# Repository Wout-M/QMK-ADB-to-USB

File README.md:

# QMK ADB to USB Converter
A custom ADB to USB Converter with an OLED screen, made with QMK, for my vintage [Apple Standard Keyboard](https://deskthority.net/wiki/Apple_Standard_Keyboard)

Special thanks to [tzarc](https://github.com/tzarc) for making the firmware of the converter & [ronangaillard](https://github.com/ronangaillard) for making the PCB.

## About the project
This all started when I wanted to try out vintage mechanical keyboards and found an Apple Standard Keyboard on a second hand site for cheap. Documentation & resources about converters that I found was very spread out or old so I decided to centralize my findings on here for if other people would try the same.

## Goals
- Being able to connect the keyboard with USB, preferably USB-C
- Fully programmable with multiple layers with QMK
- Display info about the current layer and capslock & numlock on an OLED screen

## Firmware
Using QMK was a must for me to have the keyboard be easily programmable (and already having a little experience with it helped too). Luckily, someone else also made [a converter](https://github.com/qmk/qmk_firmware/tree/master/keyboards/converter/adb_usb) on the QMK repository that I needed to customize for use with an OLED screen and the Apple Standard Keyboard (it was made mainly for the Apple Extended Keyboard).

### Wiring
For wiring the ADB socket to the Arduino, only 3 wires are necessary for conversion (the power SW pin is not used): 

      ,--_--.
     / o4 3o \      1: DATA
    | o2   1o |     2: Power SW
     -  ===  -      3: VCC
      `-___-'       4: GND

    Keyboard       Converter
                   ,------.
    VCC-----+------|5V    |
            |      |      |
           [R]     |      |
            |      |      |
    DATA----+------|PD0   |
                   |      |
    GND------------|GND   |
                   `------'
    R: 1K Ohm resistor

I'll be using an Arduino Pro Micro for this, where pin PD0 is pin 3 (D0 on the image).

Sadly, this pin is also for I2C communication (which I will need for the OLED screen), but luckily the pin for the converter can be customized by changing the value for `ADB_DATA_BIT` in `config.h` where 0 stands for pin PD0 so changing it to 2 will make it use pin PD2 (pin 0 on the Pro Micro).

For the OLED screen I'll be using pins 2 (SDA) and 3 (SCL) for the I2C communication. This also requires adding a few things in the firmware files:
- `rules.mk`: Add `OLED_ENABLE = yes`
- `config.h`: If any changes need to be made to QMK's default OLED configuration, they should be made here. I added `#define OLED_TIMEOUT 0` to have the screen always on
- `keymap.c`: In your keymap file you'll need to add the necessary functions to display what you want on the screen.
    ```c
    #ifdef OLED_ENABLE

    bool oled_task_user(void) {
        // Host Keyboard Layer Status
        // oled_write_P(PSTR("Layer: "), false);

        switch (get_highest_layer(layer_state)) {
            case 0:
                oled_write_ln_P(PSTR("DEFAULT\n"), false);
                break;
            case 1:
                oled_write_ln_P(PSTR("FUNCTION\n"), false);
                break;
            default:
                // Or use the write_ln shortcut over adding '\n' to the end of your string
                oled_write_ln_P(PSTR("Undefined"), false);
        }

        // Host Keyboard LED Status
        led_t led_state = host_keyboard_led_state();
        oled_write_P(led_state.num_lock ? PSTR("NUM ") : PSTR("    "), false);
        oled_write_P(led_state.caps_lock ? PSTR("CAP ") : PSTR("    "), false);
        oled_write_P(led_state.scroll_lock ? PSTR("SCR ") : PSTR("    "), false);
        
        return false;
    }

    oled_rotation_t oled_init_user(oled_rotation_t rotation) {
        return OLED_ROTATION_180;  // flips the display 180 degrees if offhand
    }

    #endif
    ```

### Layers
Since the Apple Standard Keyboard doesn't have a function row and the extra buttons of a full sized keyboard (home, end, pg up/down, ...) that I use while developing, I wanted to have atleast 2 layers.

One with the normal keys shown on the keycaps

And one with all the special keys

### Building the firmware
In the [QMK docs](https://docs.qmk.fm) you can find plenty of information on what you'll need to be able to build the firmware and how to flash it, but in short you'll need:

- `QMK MSYS`: For building the firmware. 
    - Use `qmk setup` for setting up the qmk_firmware folder where all keyboards, keymaps & logic is contained. By default it's installed under your user folder.
    - For the converter code, you'll find it at `keyboards/converter/adb_usb` (and replace the files with those from this repo if you want to use my code)
    - I've used the following command to build the firmware: `qmk compile -kb converter/adb_usb/rev1 -km default`
- `QMK Toolbox`: For flashing the firmware onto the Arduino
- Some IDE or text editor for customizing the firmware, I've used `Visual Studio Code`

## Converter
I couldn't just leave an Arduino, a port, a resistors and some wires dangling between my keyboard and my pc (even though that's what I did for a while), so I went looking into making a PCB design. 

### PCB
Luckily, once again, [somebody else](https://github.com/ronangaillard/adb2usb) made *almost* what I needed. A PCB for the Arduino Pro Micro and the ADB port, but without the OLED screen connection.

With some slight modifications to the wiring for using a different pin for the conversion and adding the connections for the OLED screen, it looks like this:

### Parts
| Part name                                                                                                 | Price  |
| ----------------------------------------------------------------------------------------------------------| :----: |
| [Arduino Pro Micro clone](https://www.aliexpress.com/item/1005005967686665.html)                          | €3,71  |
| [Mini-Din 4-pin connector](https://www.aliexpress.com/item/1005004227811305.) (same shape as an ADB port) | €3,60  |
| [OLED screen](https://www.aliexpress.com/item/1005005865476967.html)                                      | €2,11  |
| [Resistor](https://www.aliexpress.com/item/32505894332.html)                                              | €1,58  |
| Custom PCB (ordered from [JLCPCB](https://jlcpcb.com/))                                                   | €1,83  |

*The list is excluding shipping cost and prices may change over time. Some parts (like the resistors) were purchased more than what I need so I would have some spares/stock.*

## Housing
I wanted the converter to be easily clipped on to the keyboard so it wouldn't get anywhere while using it while also not modifying the keyboard itself. The housing consists of 3 parts: the clip, the converter housing that slots into the clip and the OLED housing that slots into the converter housing. Everything was made with [OnShape](https://www.onshape.com).

## Build Log
### 5 September 2023
The keyboard was acquired and the idea was born.

Some inspection to see if the board itself still looks good:

### 11 November 2023
After a small hiatus & many evenings of research and trying out different things, the keyboard finally works.

For now, the converter is held together with wires and tape, but the initial PCB (without OLED) is on it's way.

Now the deep cleaning of the keyboard can start (30 years worth of dust and grime isn't going to come off by itself). I can highly recommend [this video](https://www.youtube.com/watch?v=RnvC80Vjuts) for tips on how to clean vintage keyboards. 

I've used lots of Q-tips & isopropyl alcohol for the keyboard itself and a soap bath of a couple days for the keycaps. One of the keycaps on the numpad was sadly severely damaged on the inside (the pin was glued on with hot glue) so I decided to leave it off since I won't use it anyways.

### 4 December 2023
After a long wait, and some problems with delivery, the PCB with the OLED connector is here.

I recommend using some male & female pin headers for the OLED screen. This way you can just slide the screen in the top housing and easily put it on or take it off without worrying about breaking connections.

### 8 December 2023
Thanks to my Ender 3 and some evenings on OnShape, the full housing is now finished to and I can actually properly use my keyboard instead of having a taped together wire & bare electronics mess.

I've been using this keyboard every day at work ever since.

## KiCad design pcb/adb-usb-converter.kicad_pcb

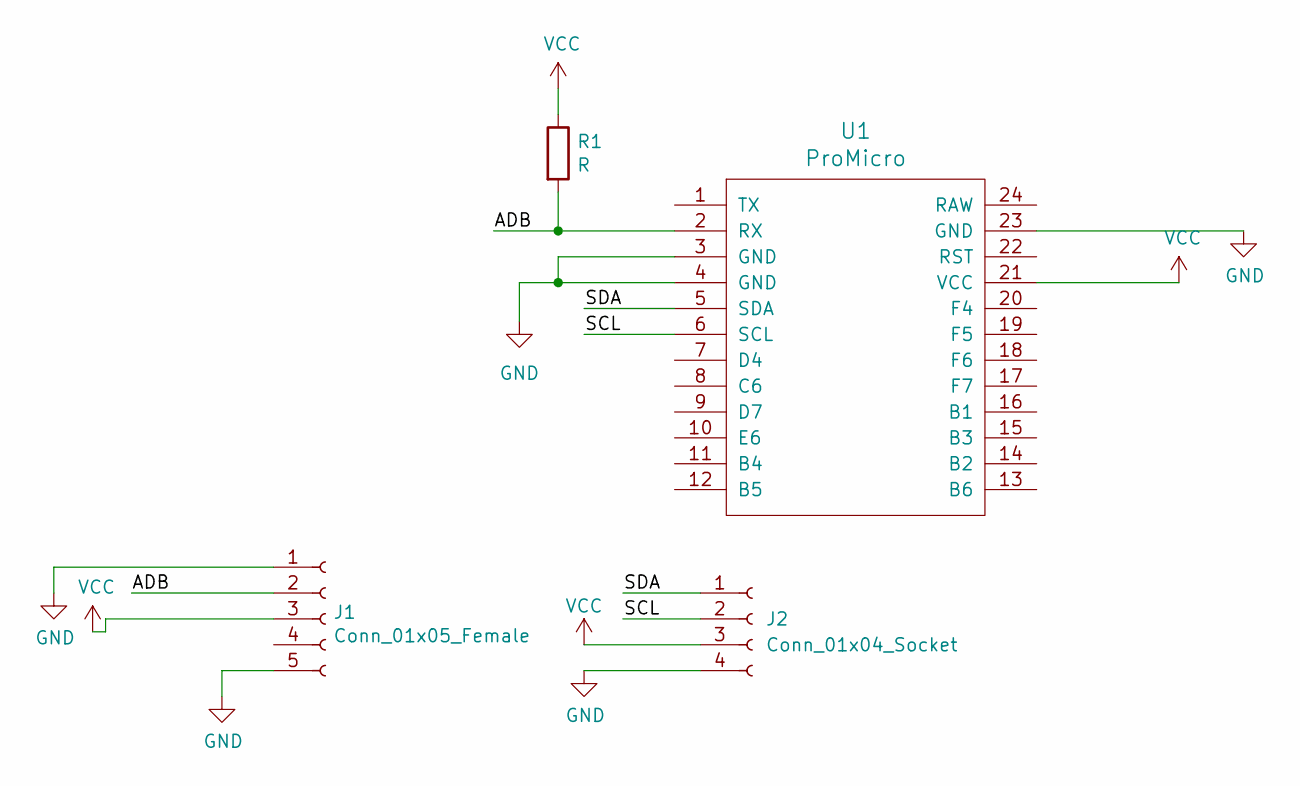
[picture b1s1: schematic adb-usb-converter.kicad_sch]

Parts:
J1: Conn_01x05_Female; adb_connector
J2: Conn_01x04_Socket; PinHeader_1x04_P2.54mm_Vertical
R1: R; R_Axial_DIN0204_L3.6mm_D1.6mm_P7.62mm_Horizontal
U1: ProMicro; ProMicro-NoSilk

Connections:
/ADB: J1.2, R1.2, U1.2 (RX)
/SCL: J2.2, U1.6 (SCL)
/SDA: J2.1, U1.5 (SDA)
GND: J1.1, J1.5, J2.4, U1.3 (GND), U1.4 (GND), U1.23 (GND)
VCC: J1.3, J2.3, R1.1, U1.21 (VCC)

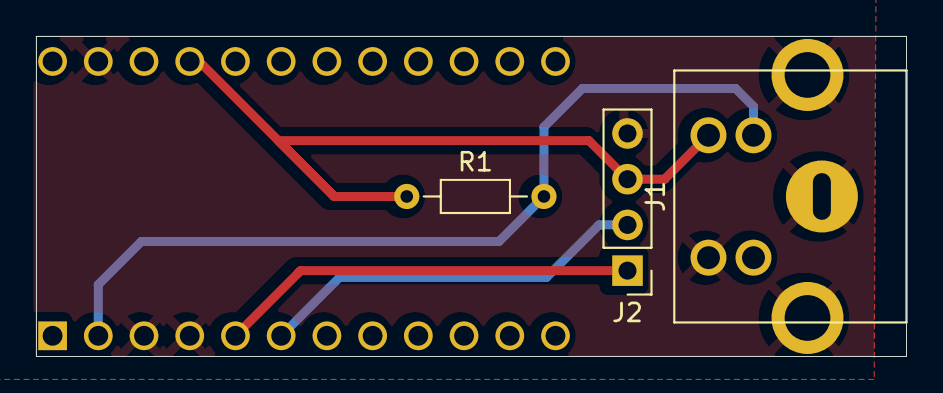
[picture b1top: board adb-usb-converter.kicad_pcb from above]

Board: 2 copper layers, 48.3 x 17.8 mm, 4 parts (0 on the bottom side), 5 nets.

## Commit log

2024-01-21 Add everything
2024-01-21 Remove excess keymaps & update readme
2024-01-21 Rename PCB.png to pcb.png
